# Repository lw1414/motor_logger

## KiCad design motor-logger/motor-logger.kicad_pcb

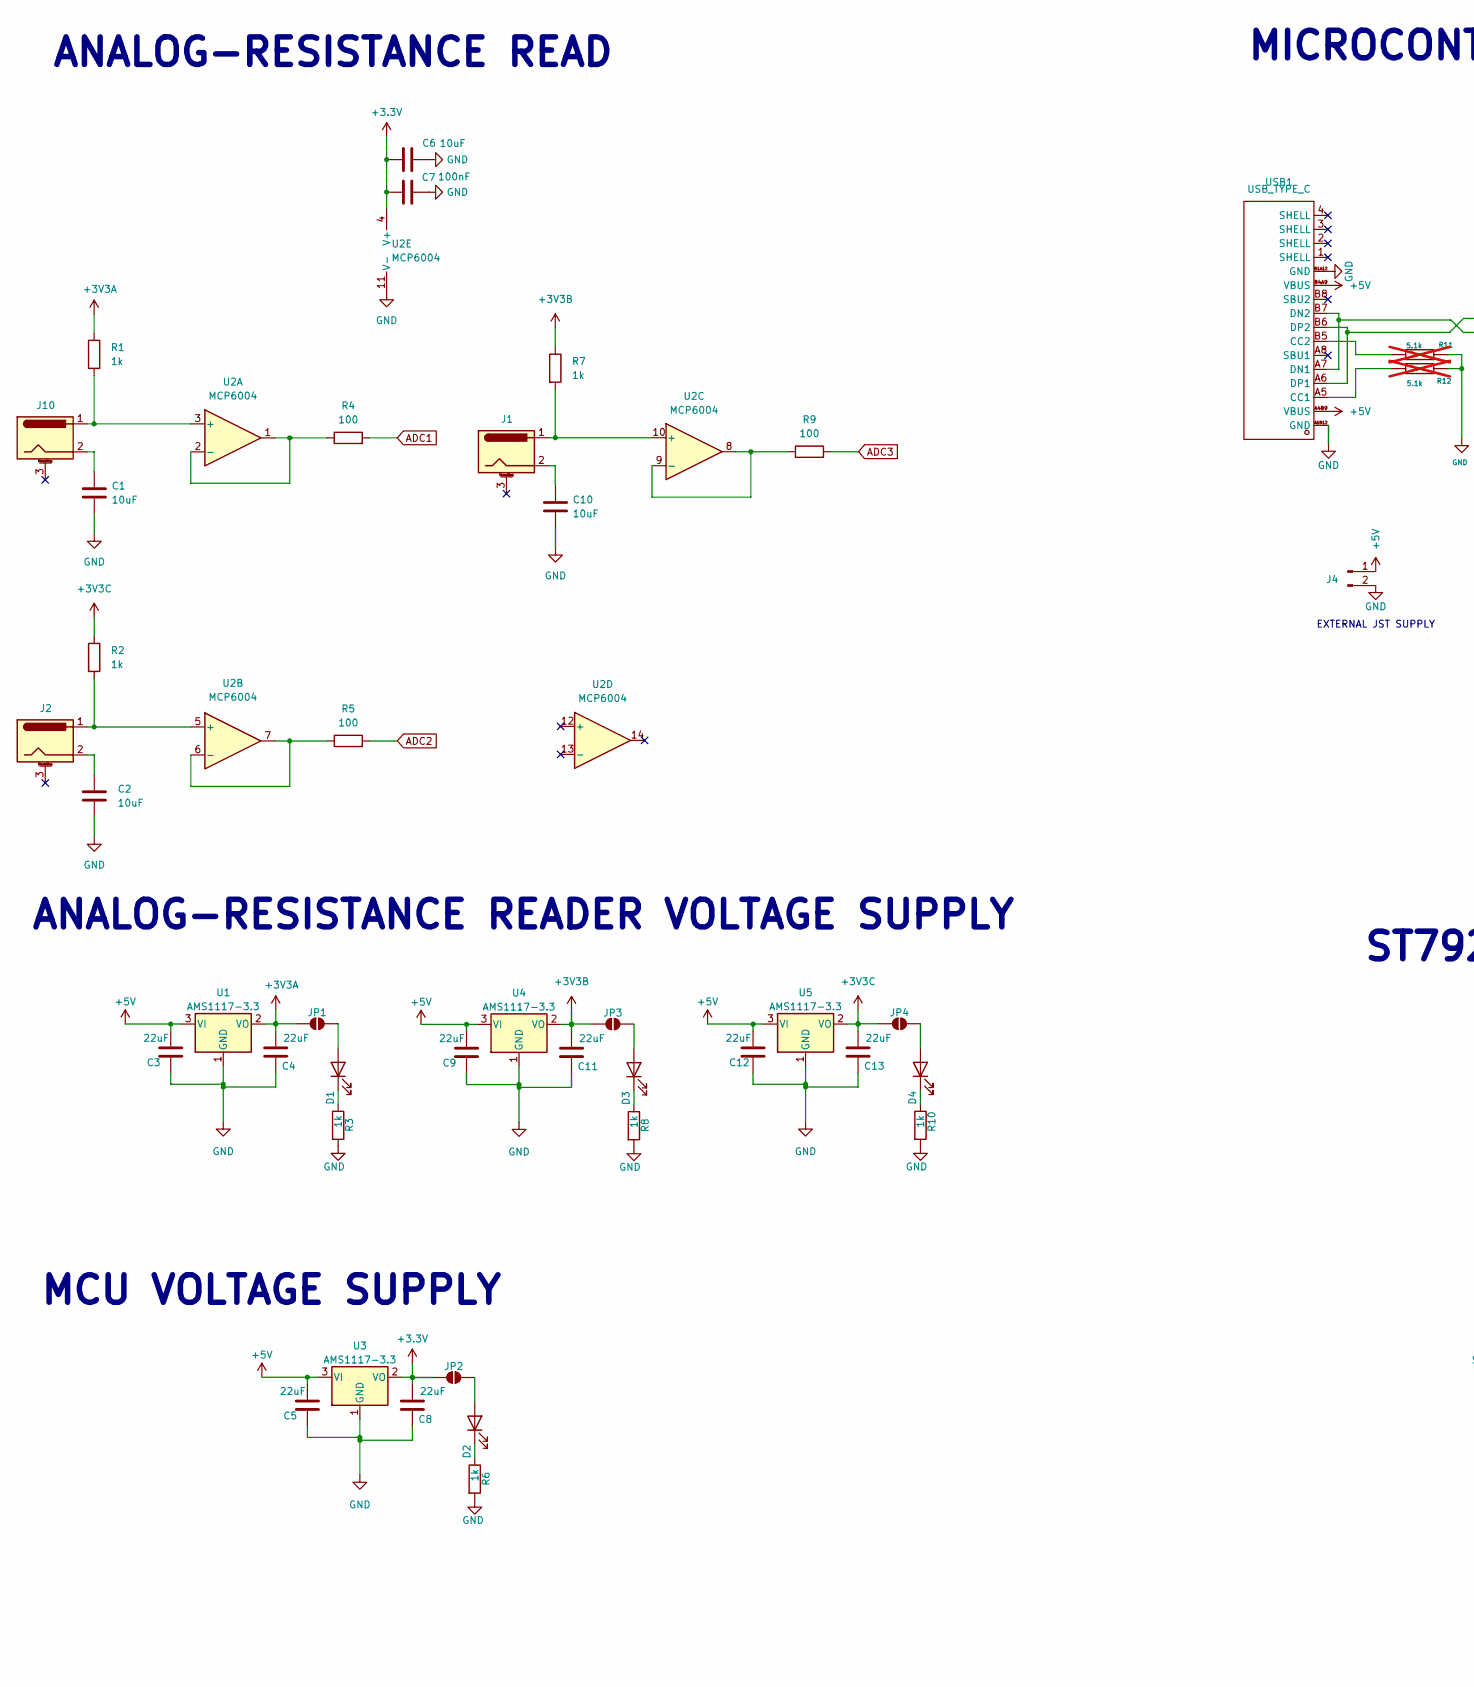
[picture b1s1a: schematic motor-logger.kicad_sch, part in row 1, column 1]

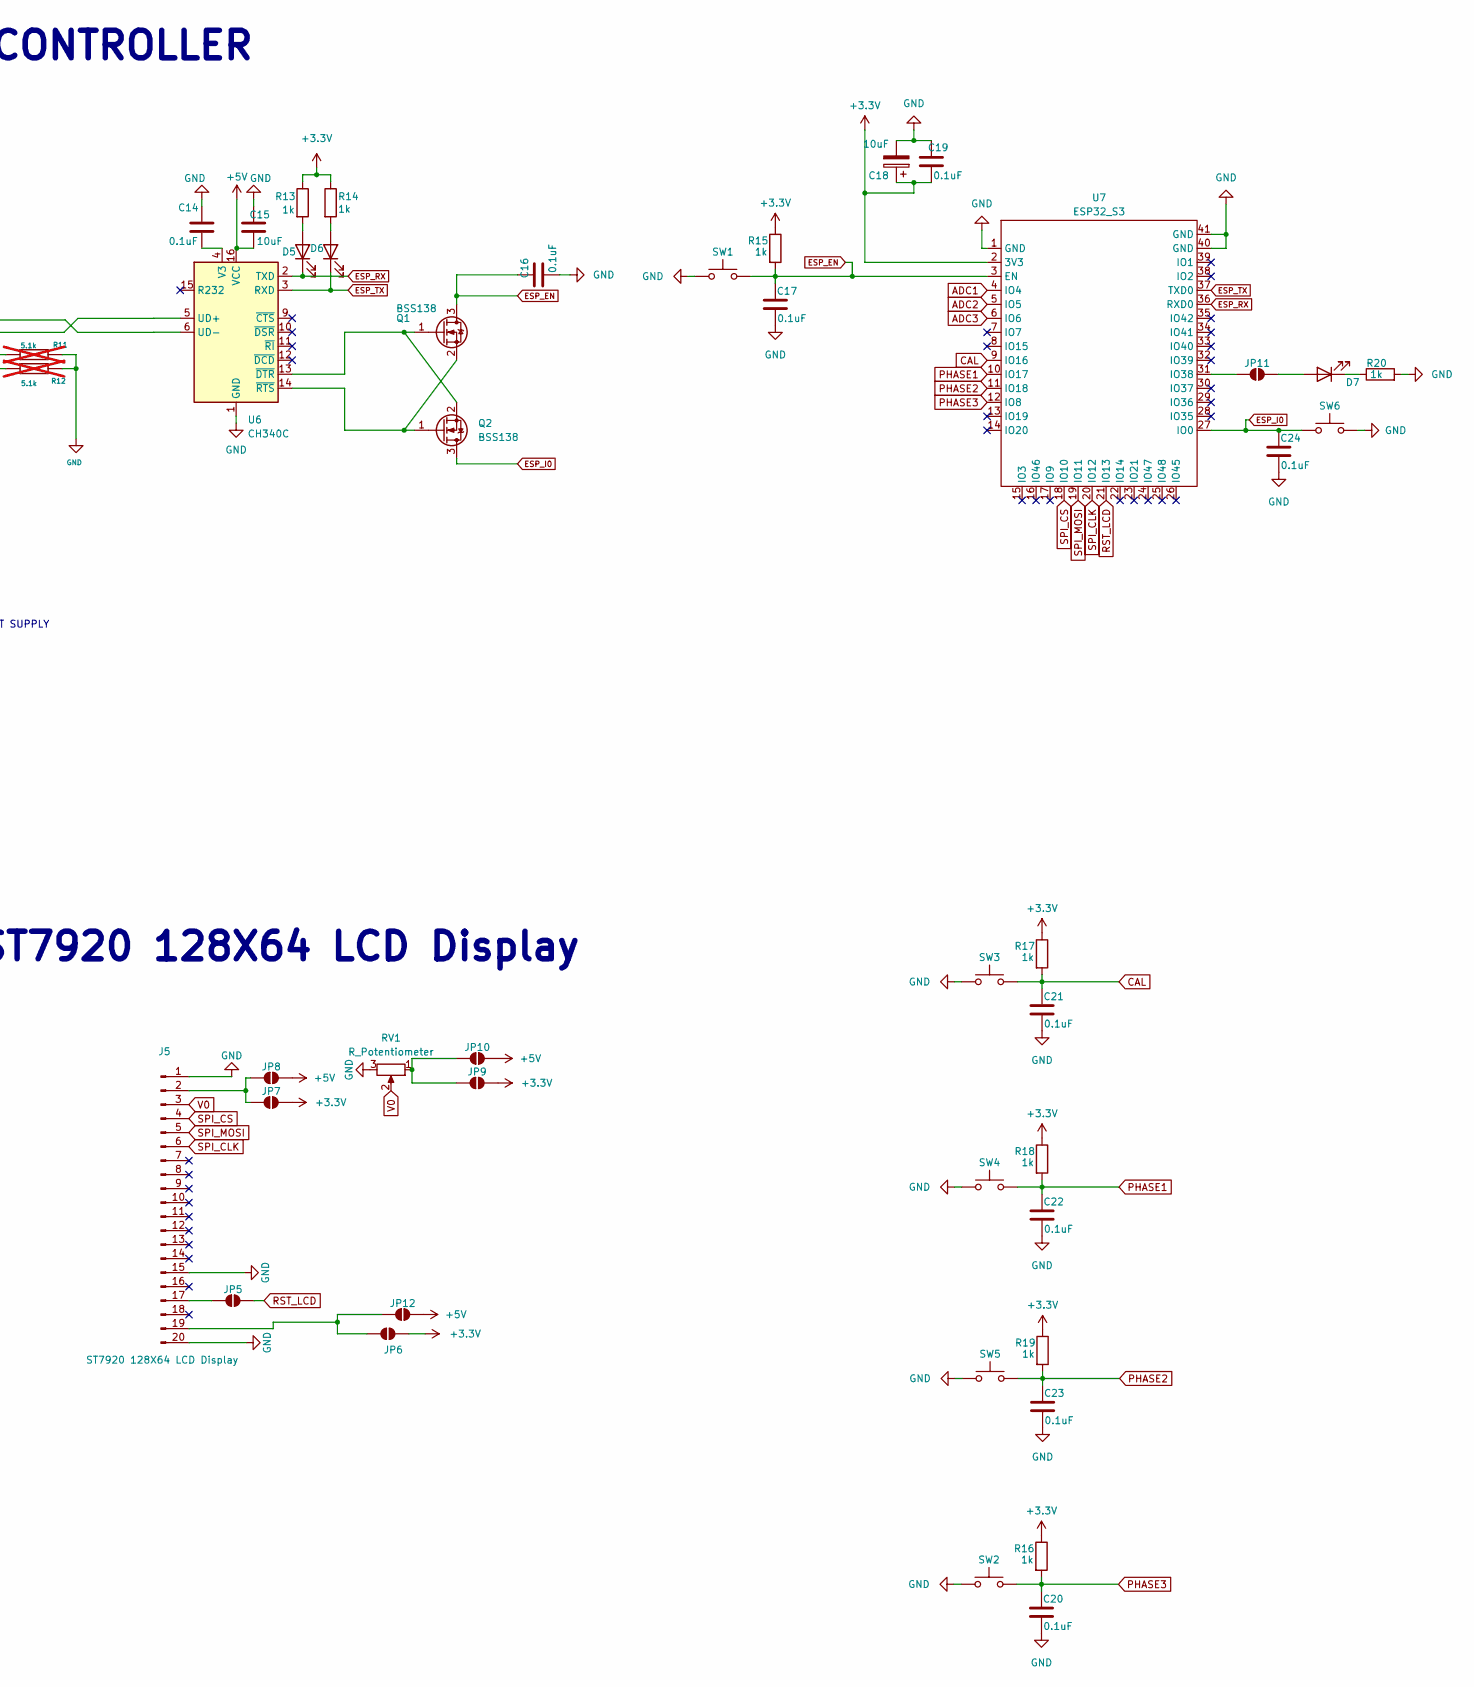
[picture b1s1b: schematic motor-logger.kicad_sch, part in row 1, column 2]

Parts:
C1, C2, C6, C10, C15, C18: 10uF; C_0805_2012Metric_Pad1.18x1.45mm_HandSolder; LCSC C15850
C3, C4, C5, C8, C9, C11, C12, C13: 22uF; C_0603_1608Metric; LCSC C59461
C7: 100nF; C_0805_2012Metric_Pad1.18x1.45mm_HandSolder; LCSC C49678
C14, C16, C17, C19, C20, C21, C22, C23, C24: 0.1uF; C_0805_2012Metric_Pad1.18x1.45mm_HandSolder; LCSC C49678
D1, D2, D3, D4, D5, D6, D7: LED; LED_0805_2012Metric_Pad1.15x1.40mm_HandSolder; LCSC C2297
J1, J2, J10: Barrel_Jack_MountingPin; BarrelJack_GCT_DCJ200-10-A_Horizontal
J4: Conn_01x02_Pin; TerminalBlock_MaiXu_MX126-5.0-02P_1x02_P5.00mm
J5: ST7920 128X64 LCD Display; LCD-TH_HS12864-15C
JP1, JP2, JP3, JP4, JP5, JP6, JP7, JP8, JP9, JP10, JP11, JP12: SolderJumper_2_Open; SolderJumper-2_P1.3mm_Open_RoundedPad1.0x1.5mm
Q1, Q2: BSS138; SOT-23; LCSC C426569
R1, R2, R7: 1k; R_0805_2012Metric_Pad1.20x1.40mm_HandSolder; LCSC C21190
R3, R6, R8, R10, R13, R14, R15, R16, R17, R18, R19, R20: 1k; R_0603_1608Metric_Pad0.98x0.95mm_HandSolder; LCSC C21190
R4, R5, R9: 100; R_0805_2012Metric_Pad1.20x1.40mm_HandSolder; LCSC C105588
R11, R12: 5.1k; R_0603_1608Metric_Pad0.98x0.95mm_HandSolder; LCSC C103079; not fitted
RV1: R_Potentiometer; RES-ADJ-SMD_3P-L3.0-W3.8-P1.75-BR; LCSC C719176
SW1, SW6: SW_Push; SW_Tactile_SPST_NO_Straight_CK_PTS636Sx25SMTRLFS; LCSC C2689642
SW2, SW3, SW4, SW5: SW_Push; SW_PUSH_6mm_H9.5mm; LCSC C2689642
U1, U3, U4, U5: AMS1117-3.3; SOT-223-3_TabPin2; LCSC C5199435
U2: MCP6004; SOIC-14_3.9x8.7mm_P1.27mm; LCSC C7378
U6: CH340C; SOP-16_3.9x9.9mm_P1.27mm; LCSC C84681
U7: ESP32_S3; WIRELM-SMD_ESP32-S3-WROOM-1; Manufacturer Part ESP32-S3-WROOM-1-N16R2; LCSC Part Name 通用型Wi-Fi+低功耗蓝牙MCU模组
USB1: USB_TYPE_C; USB-C-SMD_TYPE-C16PIN; Manufacturer Part TYPE-C16PIN; LCSC Part Name Type-C 母 卧贴

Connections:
+3.3V: C6.1, C7.1, C8.2, C18.1, C19.1, JP2.1 (A), JP6.2 (B), JP7.2 (B), JP9.2 (B), R13.1, R14.1, R15.1, R16.1, R17.1, R18.1, R19.1, U2.4 (V+), U3.2 (VO), U7.2 (3V3)
+3V3A: C4.2, JP1.1 (A), R1.1, U1.2 (VO)
+3V3B: C11.2, JP3.1 (A), R7.1, U4.2 (VO)
+3V3C: C13.2, JP4.1 (A), R2.1, U5.2 (VO)
+5V: C3.2, C5.2, C9.2, C12.2, C15.1, J4.1, JP8.2 (B), JP10.2 (B), JP12.2 (B), U1.3 (VI), U3.3 (VI), U4.3 (VI), U5.3 (VI), U6.16 (VCC), USB1.A4B9 (VBUS), USB1.B4A9 (VBUS)
ADC1: R4.2, U7.4 (IO4)
ADC2: R5.2, U7.5 (IO5)
ADC3: R9.2, U7.6 (IO6)
CAL: C21.2, R17.2, SW3.2, U7.9 (IO16)
ESP_EN: C16.2, C17.2, Q1.3 (D), R15.2, SW1.2, U7.3 (EN)
ESP_I0: C24.2, Q2.3 (D), SW6.1, U7.27 (IO0)
ESP_RX: D5.1 (K), U6.2 (TXD), U7.36 (RXD0)
ESP_TX: D6.1 (K), U6.3 (RXD), U7.37 (TXD0)
GND: C1.2, C2.2, C3.1, C4.1, C5.1, C6.2, C7.2, C8.1, C9.1, C10.2, C11.1, C12.1, C13.1, C14.2, C15.2, C16.1, C17.1, C18.2, C19.2, C20.1, C21.1, C22.1, C23.1, C24.1, J4.2, J5.1, J5.15, J5.20, R3.2, R6.2, R8.2, R10.2, R11.2, R12.2, R20.2, RV1.3, SW1.1, SW2.1, SW3.1, SW4.1, SW5.1, SW6.2, U1.1 (GND), U2.11 (V-), U3.1 (GND), U4.1 (GND), U5.1 (GND), U6.1 (GND), U7.1 (GND), U7.40 (GND), U7.41 (GND), USB1.A1B12 (GND), USB1.B1A12 (GND)
unnamed: C1.1, J10.2
unnamed: C2.1, J2.2
unnamed: C10.1, J1.2
unnamed: D1.2 (A), JP1.2 (B)
unnamed: D1.1 (K), R3.1
unnamed: D2.2 (A), JP2.2 (B)
unnamed: D2.1 (K), R6.1
unnamed: D3.2 (A), JP3.2 (B)
unnamed: D3.1 (K), R8.1
unnamed: D4.2 (A), JP4.2 (B)
unnamed: D4.1 (K), R10.1
unnamed: D5.2 (A), R13.2
unnamed: D6.2 (A), R14.2
unnamed: D7.2 (A), JP11.2 (B)
unnamed: D7.1 (K), R20.1
unnamed: J5.2, JP7.1 (A), JP8.1 (A)
unnamed: J5.17, JP5.1 (A)
unnamed: J5.19, JP6.1 (A), JP12.1 (A)
unnamed: JP9.1 (A), JP10.1 (A), RV1.1
unnamed: JP11.1 (A), U7.31 (IO38)
unnamed: Q1.1 (G), Q2.2 (S), U6.13 (~DTR)
unnamed: Q1.2 (S), Q2.1 (G), U6.14 (~RTS)
unnamed: J10.1, R1.2, U2.3 (+)
unnamed: R4.1, U2.1, U2.2 (-)
unnamed: J2.1, R2.2, U2.5 (+)
unnamed: R5.1, U2.6 (-), U2.7
unnamed: J1.1, R7.2, U2.10 (+)
unnamed: R9.1, U2.8, U2.9 (-)
unnamed: U6.5 (UD+), USB1.A6 (DP1), USB1.B6 (DP2)
unnamed: U6.6 (UD-), USB1.A7 (DN1), USB1.B7 (DN2)
unnamed: C14.1, U6.4 (V3)
unnamed: R12.1, USB1.A5 (CC1)
unnamed: R11.1, USB1.B5 (CC2)
PHASE1: C22.2, R18.2, SW4.2, U7.10 (IO17)
PHASE2: C23.2, R19.2, SW5.2, U7.11 (IO18)
PHASE3: C20.2, R16.2, SW2.2, U7.12 (IO8)
RST_LCD: JP5.2 (B), U7.21 (IO13)
SPI_CLK: J5.6, U7.20 (IO12)
SPI_CS: J5.4, U7.18 (IO10)
SPI_MOSI: J5.5, U7.19 (IO11)
V0: J5.3, RV1.2

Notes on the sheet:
MCU VOLTAGE SUPPLY
MICROCONTROLLER
ANALOG-RESISTANCE READ
ST7920 128X64 LCD Display
EXTERNAL JST SUPPLY
ANALOG-RESISTANCE READER VOLTAGE SUPPLY

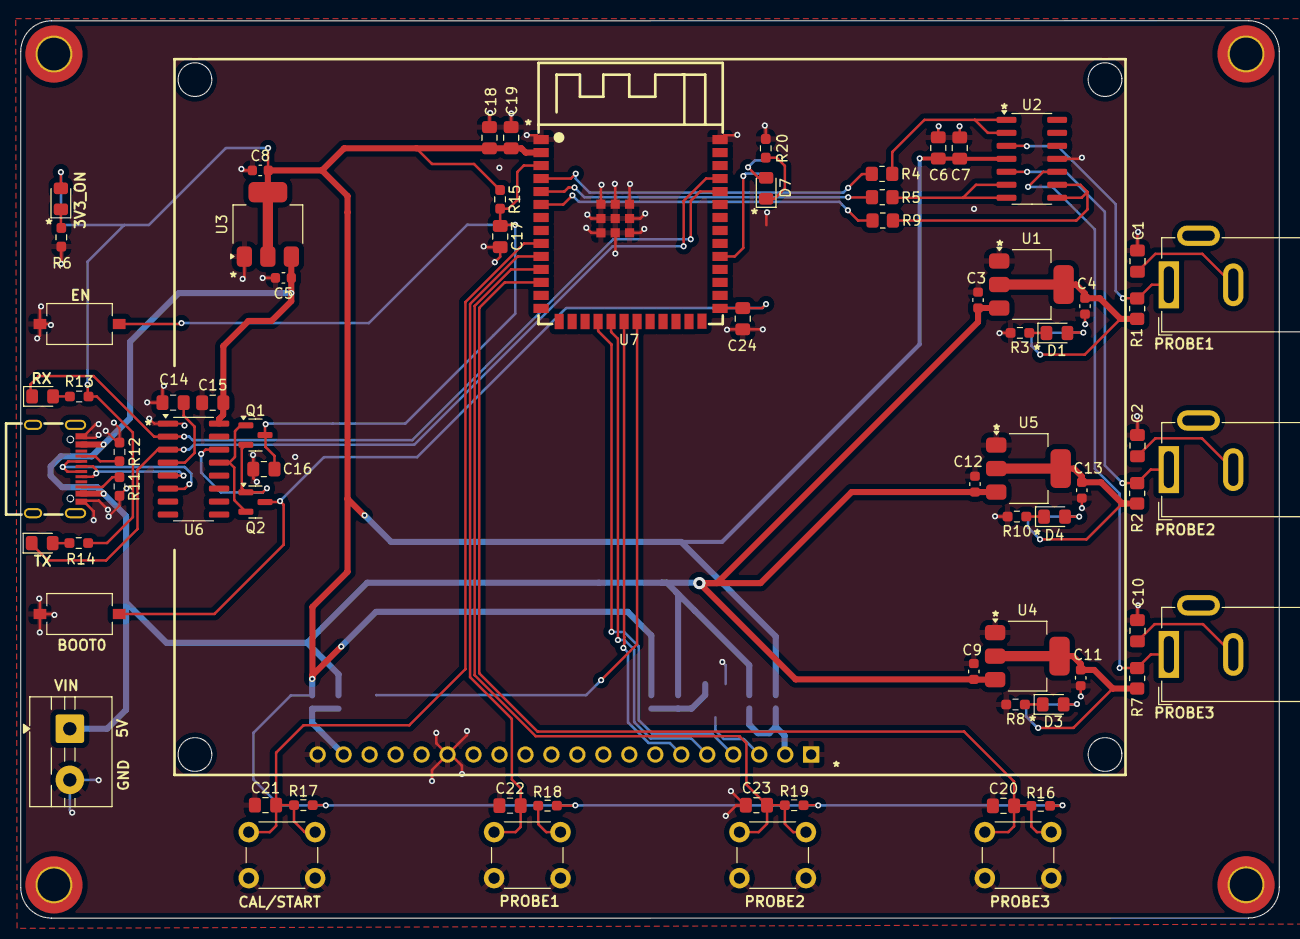
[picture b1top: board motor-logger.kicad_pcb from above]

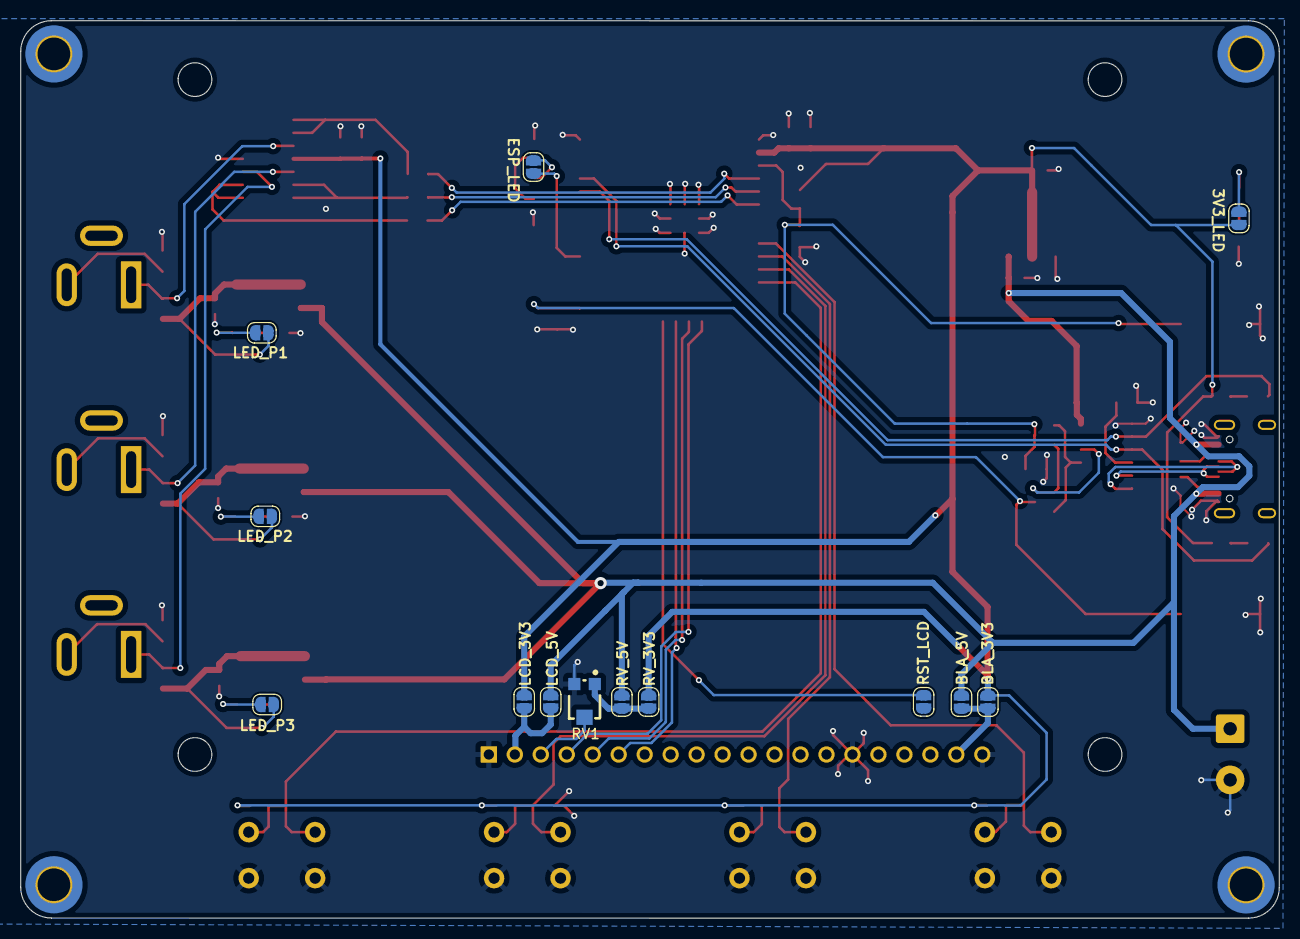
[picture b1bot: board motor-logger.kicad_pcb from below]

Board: 2 copper layers, 123.1 x 87.8 mm, 85 parts (13 on the bottom side), 55 nets.
